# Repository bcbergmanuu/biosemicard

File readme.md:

# biosemi expansion card

v2:

v2:

Opamp OPA2188: [Datasheet](https://www.ti.com/lit/ds/symlink/opa2188.pdf?ts=1748075346926).
ADC: [Datasheet](https://www.ti.com/lit/ds/symlink/ads1254.pdf?ts=1747838598927).

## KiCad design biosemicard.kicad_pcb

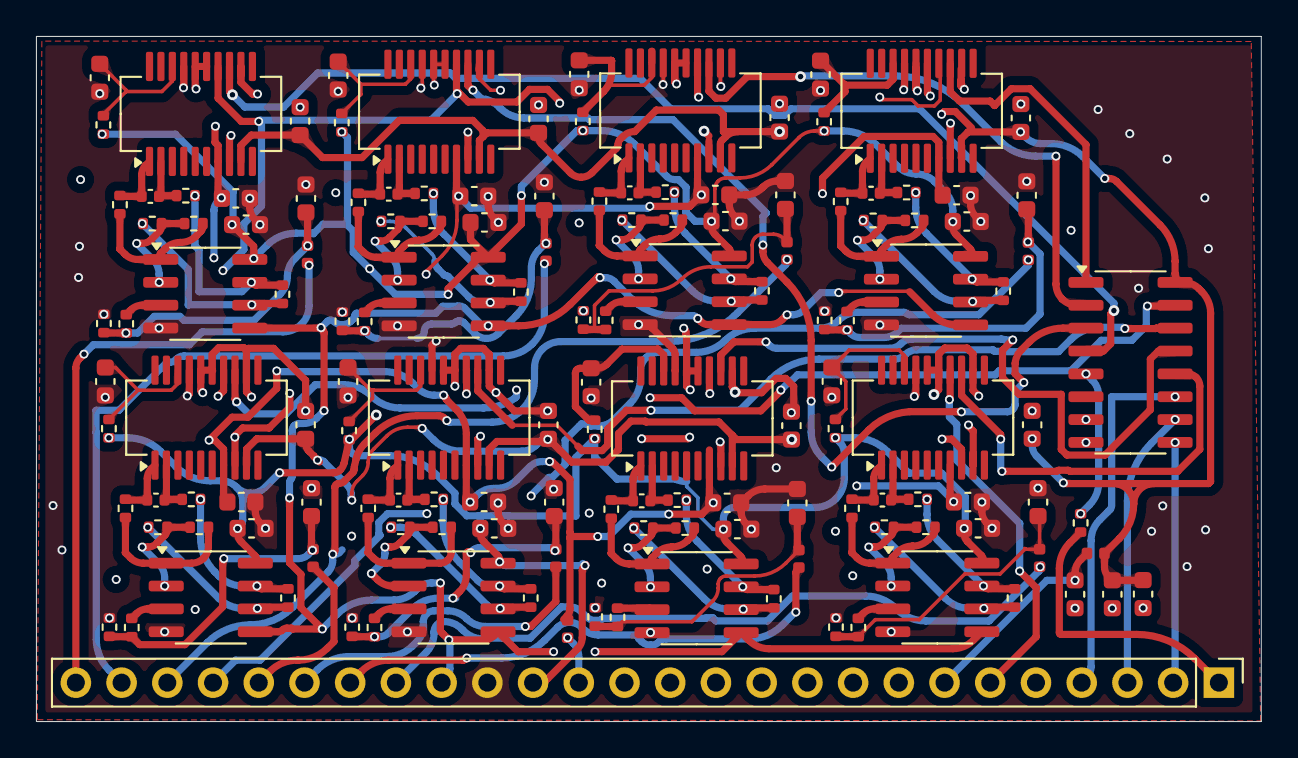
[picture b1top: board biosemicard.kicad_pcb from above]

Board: 4 copper layers, 68.1 x 38.1 mm, 144 parts (0 on the bottom side), 103 nets.

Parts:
C1, C4, C5, C6, C7, C9, C10, C11, C12, C13, C14, C16, C17, C18, C19, C21, C22, C23, C24, C26, C27, C28, C29, C31, C32, C33, C34, C36, C37, C38, C39, C41: 10u; C_0603_1608Metric
C2, C8, C15, C20, C25, C30, C35, C40: 20n; C_0402_1005Metric
C3, C43: 1u; C_0603_1608Metric
C42, C44, C45, C46, C47, C48, C49, C50, C51: 2.2u; C_0603_1608Metric
FB1, FB2, FB3, FB4, FB5, FB6, FB7, FB8, FB9, FB10: FerriteBead; L_0402_1005Metric
J1: Conn_01x26_Pin; PinHeader_1x26_P2.54mm_Vertical
R1: 24.9; R_0402_1005Metric
R2, R9, R16, R23, R30, R37, R44, R51: 3300; R_0402_1005Metric
R3, R7, R8, R10, R14, R15, R17, R21, R22, R24, R28, R29, R31, R35, R36, R38, R42, R43, R45, R49, R50, R52, R56, R57: 1k; R_0402_1005Metric
R4, R11, R18, R25, R32, R39, R46, R53: 20500; R_0402_1005Metric
R5, R12, R19, R26, R33, R40, R47, R54: 3010; R_0402_1005Metric
R6, R13, R20, R27, R34, R41, R48, R55: 23700; R_0402_1005Metric
R58, R59, R60, R61, R62, R63, R64, R65: 1500; R_0402_1005Metric
U1, U4, U6, U8, U10, U12, U14, U16: OPA2188AIDR; SOIC-8_3.9x4.9mm_P1.27mm
U2: 74HC151D; SOIC-16_3.9x9.9mm_P1.27mm
U3, U5, U7, U9, U11, U13, U15, U17: ADS1254E; QSOP-20_3.9x8.7mm_P0.635mm

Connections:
+2V5: C3.1, C6.1, C11.1, C14.1, C19.1, C24.1, C29.1, C34.1, C39.1, C42.1, FB10.1, U2.16 (VCC), U3.9 (DVDD), U5.9 (DVDD), U7.9 (DVDD), U9.9 (DVDD), U11.9 (DVDD), U13.9 (DVDD), U15.9 (DVDD), U17.9 (DVDD)
+2V048: C1.1, C7.1, C12.1, C17.1, C22.1, C27.1, C32.1, C37.1, J1.16, R8.1, R15.1, R22.1, R29.1, R36.1, R43.1, R50.1, R57.1, U1.8 (V+), U4.8 (V+), U6.8 (V+), U8.8 (V+), U10.8 (V+), U12.8 (V+), U14.8 (V+), U16.8 (V+)
+2V93: C5.1, C10.1, C13.1, C18.1, C23.1, C28.1, C33.1, C38.1, FB9.1, U3.7 (AVDD), U5.7 (AVDD), U7.7 (AVDD), U9.7 (AVDD), U11.7 (AVDD), U13.7 (AVDD), U15.7 (AVDD), U17.7 (AVDD)
-2V048: C1.2, C4.1, C5.2, C7.2, C9.1, C10.2, C12.2, C13.2, C16.1, C17.2, C18.2, C21.1, C22.2, C23.2, C26.1, C27.2, C28.2, C31.1, C32.2, C33.2, C36.1, C37.2, C38.2, C41.1, C44.2, C45.2, C46.2, C47.2, C48.2, C49.2, C50.2, C51.2, J1.17, R58.2, R59.2, R60.2, R61.2, R62.2, R63.2, R64.2, R65.2, U1.4 (V-), U3.17 (AGND), U4.4 (V-), U5.17 (AGND), U6.4 (V-), U7.17 (AGND), U8.4 (V-), U9.17 (AGND), U10.4 (V-), U11.17 (AGND), U12.4 (V-), U13.17 (AGND), U14.4 (V-), U15.17 (AGND), U16.4 (V-), U17.17 (AGND)
/Ain0: FB1.2, J1.26
/Ain1: FB2.2, J1.25
/Ain2: FB3.2, J1.24
/Ain3: FB4.2, J1.23
/Ain4: FB5.2, J1.22
/Ain5: FB6.2, J1.21
/Ain6: FB7.2, J1.20
/Ain7: FB8.2, J1.19
/DOUT0: U2.4 (I0), U3.13 (DOUT/~DRDY)
/DOUT1: U2.3 (I1), U5.13 (DOUT/~DRDY)
/DOUT2: U2.2 (I2), U7.13 (DOUT/~DRDY)
/DOUT3: U2.1 (I3), U9.13 (DOUT/~DRDY)
/DOUT4: U2.15 (I4), U11.13 (DOUT/~DRDY)
/DOUT5: U2.14 (I5), U13.13 (DOUT/~DRDY)
/DOUT6: U2.13 (I6), U15.13 (DOUT/~DRDY)
/DOUT7: U2.12 (I7), U17.13 (DOUT/~DRDY)
/S0: J1.4, U2.11 (S0)
/S1: J1.3, U2.10 (S1)
/S2: J1.2, U2.9 (S2)
/Y: R1.1, U2.5 (Y)
CLOCK: J1.5, U3.8 (CLK), U5.8 (CLK), U7.8 (CLK), U9.8 (CLK), U11.8 (CLK), U13.8 (CLK), U15.8 (CLK), U17.8 (CLK)
GND: J1.18, U1.5 (+), U4.5 (+), U6.5 (+), U8.5 (+), U10.5 (+), U12.5 (+), U14.5 (+), U16.5 (+)
GNDD: C3.2, C6.2, C11.2, C14.2, C19.2, C24.2, C29.2, C34.2, C39.2, C42.2, C43.2, J1.8, U2.7 (~E), U2.8 (GND), U3.12 (DGND), U3.15 (CHSEL1), U3.16 (CHSEL0), U5.12 (DGND), U5.15 (CHSEL1), U5.16 (CHSEL0), U7.12 (DGND), U7.15 (CHSEL1), U7.16 (CHSEL0), U9.12 (DGND), U9.15 (CHSEL1), U9.16 (CHSEL0), U11.12 (DGND), U11.15 (CHSEL1), U11.16 (CHSEL0), U13.12 (DGND), U13.15 (CHSEL1), U13.16 (CHSEL0), U15.12 (DGND), U15.15 (CHSEL1), U15.16 (CHSEL0), U17.12 (DGND), U17.15 (CHSEL1), U17.16 (CHSEL0)
unnamed: C44.1, FB1.1, R2.2, R58.1
unnamed: C45.1, FB2.1, R9.2, R59.1
unnamed: C46.1, FB3.1, R16.2, R60.1
unnamed: C47.1, FB4.1, R23.2, R61.1
unnamed: C48.1, FB5.1, R30.2, R62.1
unnamed: C49.1, FB6.1, R37.2, R63.1
unnamed: C50.1, FB7.1, R44.2, R64.1
unnamed: C51.1, FB8.1, R51.2, R65.1
unnamed: J1.1, R1.2
unnamed: C43.1, FB10.2, J1.7
unnamed: FB9.2, J1.15
unnamed: R3.2, R4.1, U1.1
unnamed: R6.1, R7.2, U1.7
unnamed: R10.2, R11.1, U4.1
unnamed: R13.1, R14.2, U4.7
unnamed: R17.2, R18.1, U6.1
unnamed: R20.1, R21.2, U6.7
unnamed: R24.2, R25.1, U8.1
unnamed: R27.1, R28.2, U8.7
unnamed: R31.2, R32.1, U10.1
unnamed: R34.1, R35.2, U10.7
unnamed: R38.2, R39.1, U12.1
unnamed: R41.1, R42.2, U12.7
unnamed: R45.2, R46.1, U14.1
unnamed: R48.1, R49.2, U14.7
unnamed: R52.2, R53.1, U16.1
unnamed: R55.1, R56.2, U16.7
unnamed: R2.1, U1.3 (+)
unnamed: R4.2, R5.1, U1.2 (-)
unnamed: R5.2, R6.2, U1.6 (-)
unnamed: C2.2, R3.1, U3.1 (CH1+)
unnamed: C2.1, R7.1, U3.2 (CH1-)
unnamed: C4.2, R8.2, U3.18 (VREF)
unnamed: R9.1, U4.3 (+)
unnamed: R11.2, R12.1, U4.2 (-)
unnamed: R12.2, R13.2, U4.6 (-)
unnamed: C8.2, R10.1, U5.1 (CH1+)
unnamed: C8.1, R14.1, U5.2 (CH1-)
unnamed: C9.2, R15.2, U5.18 (VREF)
unnamed: R16.1, U6.3 (+)
unnamed: R18.2, R19.1, U6.2 (-)
unnamed: R19.2, R20.2, U6.6 (-)
unnamed: C15.2, R17.1, U7.1 (CH1+)
unnamed: C15.1, R21.1, U7.2 (CH1-)
unnamed: C16.2, R22.2, U7.18 (VREF)
unnamed: R23.1, U8.3 (+)
unnamed: R25.2, R26.1, U8.2 (-)
unnamed: R26.2, R27.2, U8.6 (-)
unnamed: C20.2, R24.1, U9.1 (CH1+)
unnamed: C20.1, R28.1, U9.2 (CH1-)
unnamed: C21.2, R29.2, U9.18 (VREF)
unnamed: R30.1, U10.3 (+)
unnamed: R32.2, R33.1, U10.2 (-)
unnamed: R33.2, R34.2, U10.6 (-)
unnamed: C25.2, R31.1, U11.1 (CH1+)
unnamed: C25.1, R35.1, U11.2 (CH1-)
unnamed: C26.2, R36.2, U11.18 (VREF)
unnamed: R37.1, U12.3 (+)
unnamed: R39.2, R40.1, U12.2 (-)
unnamed: R40.2, R41.2, U12.6 (-)
unnamed: C30.2, R38.1, U13.1 (CH1+)
unnamed: C30.1, R42.1, U13.2 (CH1-)
unnamed: C31.2, R43.2, U13.18 (VREF)
unnamed: R44.1, U14.3 (+)
unnamed: R46.2, R47.1, U14.2 (-)
unnamed: R47.2, R48.2, U14.6 (-)
unnamed: C35.2, R45.1, U15.1 (CH1+)
unnamed: C35.1, R49.1, U15.2 (CH1-)
unnamed: C36.2, R50.2, U15.18 (VREF)
unnamed: R51.1, U16.3 (+)
unnamed: R53.2, R54.1, U16.2 (-)
unnamed: R54.2, R55.2, U16.6 (-)
unnamed: C40.2, R52.1, U17.1 (CH1+)
unnamed: C40.1, R56.1, U17.2 (CH1-)
unnamed: C41.2, R57.2, U17.18 (VREF)
SCLK: J1.6, U3.14 (SCLK), U5.14 (SCLK), U7.14 (SCLK), U9.14 (SCLK), U11.14 (SCLK), U13.14 (SCLK), U15.14 (SCLK), U17.14 (SCLK)

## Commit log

2025-05-26 first
2025-05-28 added simulation
2025-06-01 added components, updated pcb-routing
2025-06-02 layout v2
